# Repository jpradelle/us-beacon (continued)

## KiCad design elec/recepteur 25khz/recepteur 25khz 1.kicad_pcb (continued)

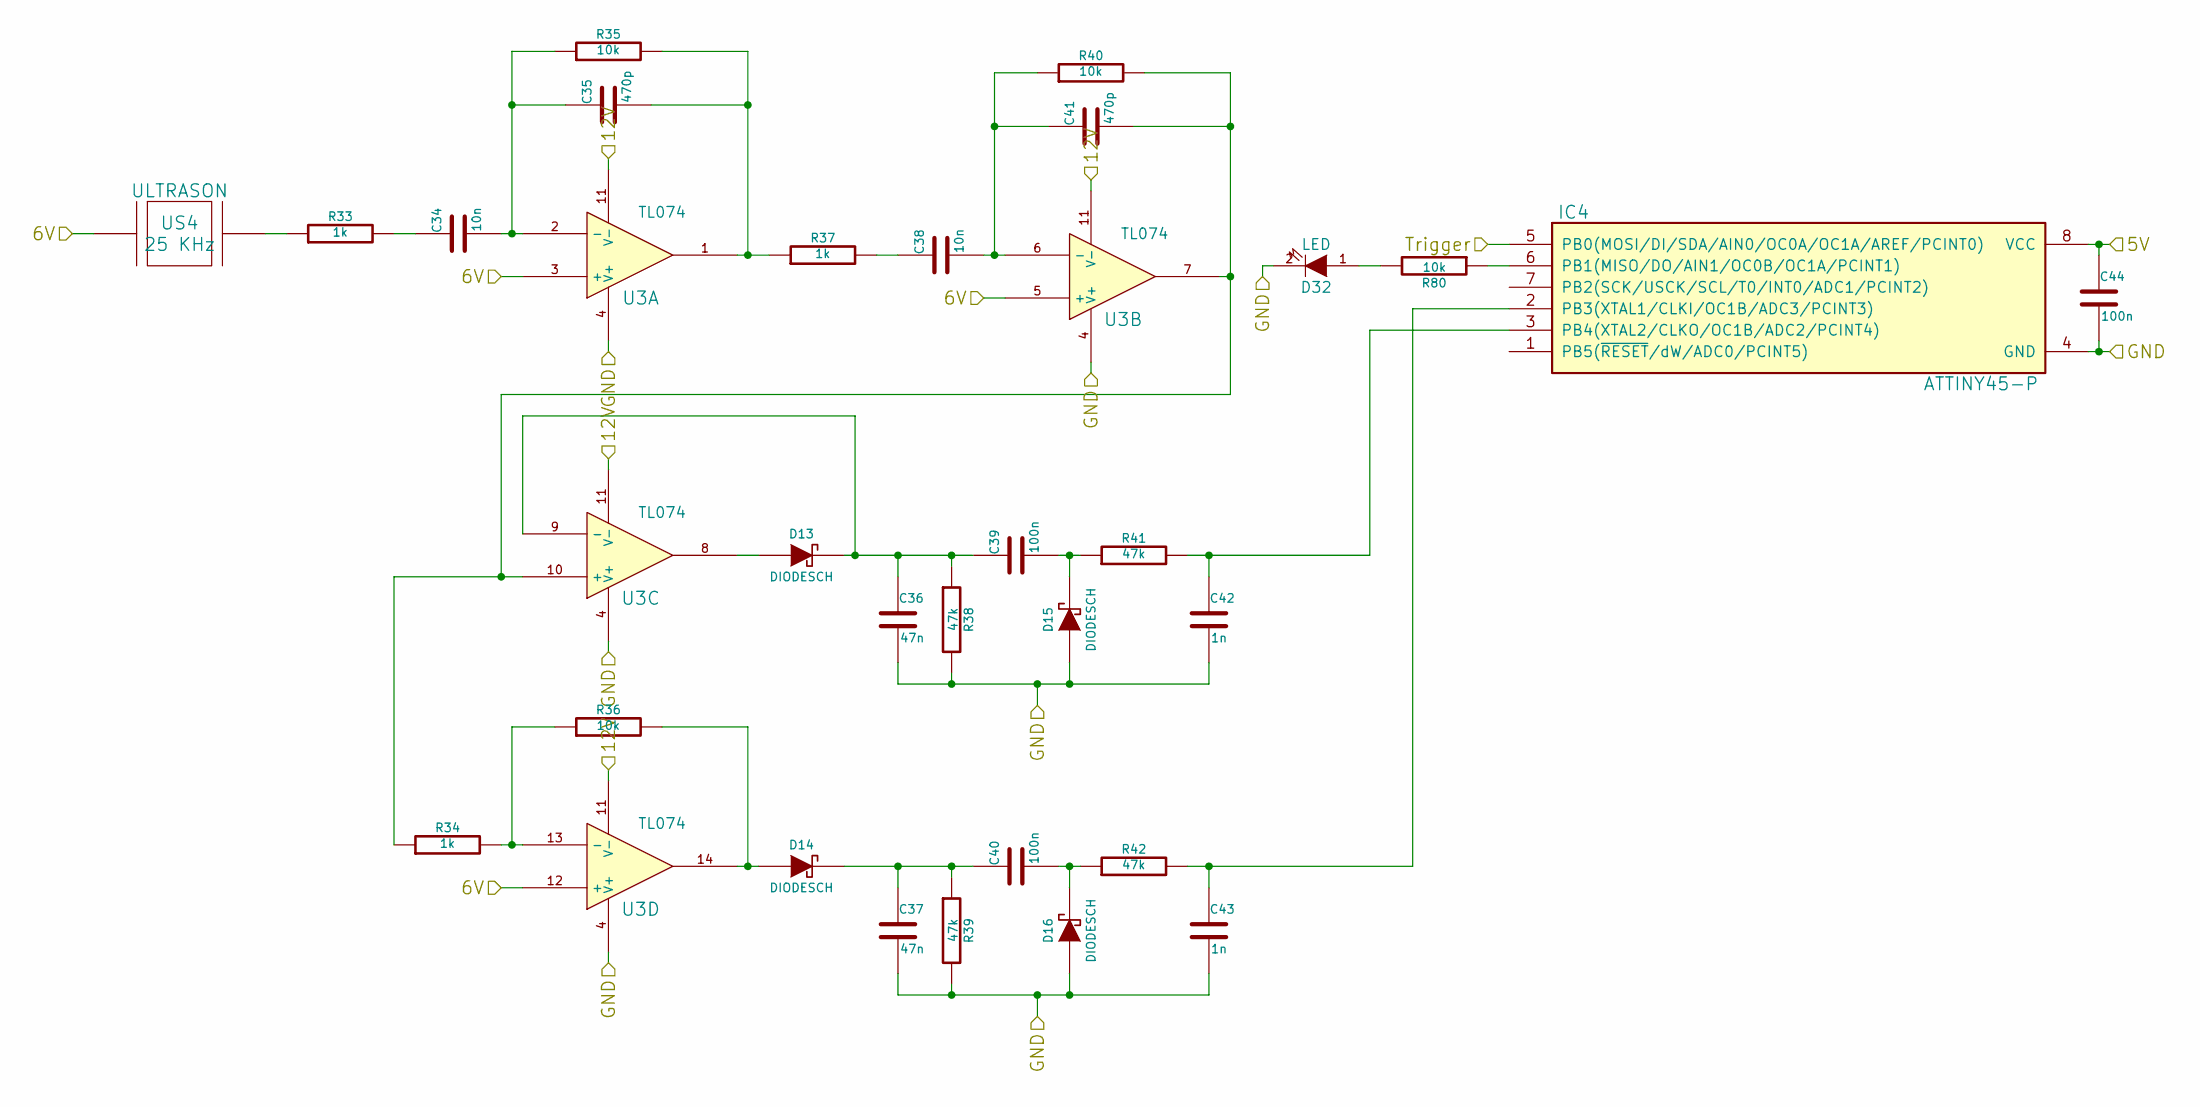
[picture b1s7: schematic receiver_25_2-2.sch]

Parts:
C34, C38: 10n
C35, C41: 470p
C36, C37: 47n
C39, C40, C44: 100n
C42, C43: 1n
D13, D14, D15, D16: DIODESCH
D32: LED
IC4: ATTINY45-P; DIP8
R33, R34, R37: 1k
R35, R36, R40, R80: 10k
R38, R39, R41, R42: 47k
U3: TL074
US4: ULTRASON

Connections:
/receiver_25_2-1/5V: C44.1, IC4.8 (VCC); also elsewhere on the board
/receiver_25_2-1/6V: U3.3 (+), U3.5 (+), U3.12 (+), US4.1; also elsewhere on the board
/receiver_25_2-1/12V: U3.11 (V-); also elsewhere on the board
/receiver_25_2-1/GND: C36.2, C37.2, C42.2, C43.2, C44.2, D15.1 (A), D16.1 (A), D32.2 (K), IC4.4 (GND), R38.2, R39.2, U3.4 (V+); also elsewhere on the board
/receiver_25_2-2/Trigger: IC4.5 (PB0(MOSI/DI/SDA/AIN0/OC0A/OC1A/AREF/PCI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); also elsewhere on the board
unnamed: C34.1, R33.2
unnamed: C34.2, C35.1, R35.1, U3.2 (-)
unnamed: C35.2, R35.2, R37.1, U3.1
unnamed: C36.1, C39.1, D13.2 (K), R38.1, U3.9 (-)
unnamed: C37.1, C40.1, D14.2 (K), R39.1
unnamed: C38.1, R37.2
unnamed: C38.2, C41.1, R40.1, U3.6 (-)
unnamed: C39.2, D15.2 (K), R41.1
unnamed: C40.2, D16.2 (K), R42.1
unnamed: C41.2, R34.1, R40.2, U3.7, U3.10 (+)
unnamed: C42.1, IC4.3 (PB4(XTAL2/CLKO/OC1B/ADC2/PCINT4)), R41.2
unnamed: C43.1, IC4.2 (PB3(XTAL1/CLKI/OC1B/ADC3/PCINT3)), R42.2
unnamed: D13.1 (A), U3.8
unnamed: D14.1 (A), R36.2, U3.14
unnamed: D32.1 (A), R80.2
unnamed: IC4.6 (PB1(MISO/DO/AIN1/OC0B/OC1A/PCINT1)), R80.1
unnamed: R33.1, US4.2
unnamed: R34.2, R36.1, U3.13 (-)

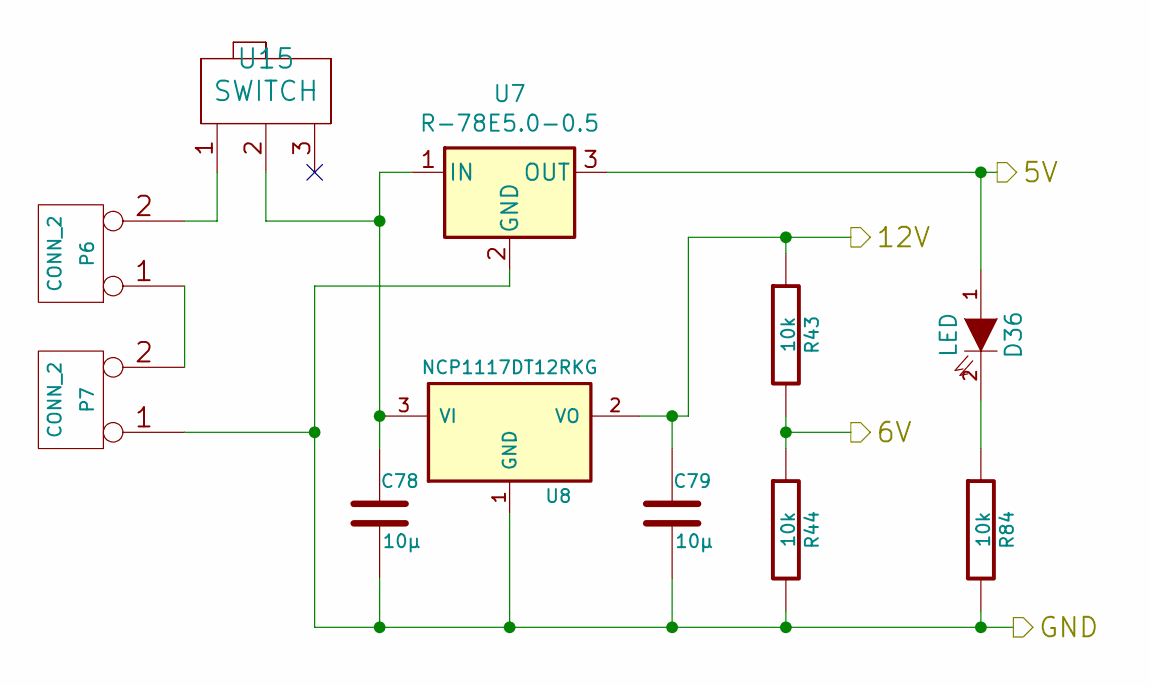
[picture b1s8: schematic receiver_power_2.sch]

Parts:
C78, C79: 10µ
D36: LED
P6, P7: CONN_2
R43, R44, R84: 10k
U7: R-78E5.0-0.5; Converter_DCDC_RECOM_R-78E-0.5_THT
U8: NCP1117DT12RKG
U15: SWITCH

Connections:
/receiver_power_2/5V: D36.1 (A), U7.3 (OUT); also elsewhere on the board
/receiver_power_2/6V: R43.2, R44.1; also elsewhere on the board
/receiver_power_2/12V: C79.1, R43.1, U8.2 (VO); also elsewhere on the board
/receiver_power_2/GND: C78.2, C79.2, P7.1, R44.2, R84.2, U7.2 (GND), U8.1 (GND); also elsewhere on the board
unnamed: C78.1, U7.1 (IN), U8.3 (VI), U15.2
unnamed: D36.2 (K), R84.1
unnamed: P6.1, P7.2 (PM)
unnamed: P6.2 (PM), U15.1

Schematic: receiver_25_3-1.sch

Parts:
C45, C49: 10n
C46, C52: 470p
C47, C48: 47n
C50, C51, C55: 100n
C53, C54: 1n
D17, D18, D19, D20: DIODESCH
D33: LED
IC5: ATTINY45-P; DIP8
R45, R46, R49: 1k
R47, R48, R52, R81: 10k
R50, R51, R53, R54: 47k
U9: TL074
US5: ULTRASON

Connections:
/receiver_25_3-1/5V: C55.1, IC5.8 (VCC); also elsewhere on the board
/receiver_25_3-1/6V: U9.3 (+), U9.5 (+), U9.12 (+), US5.1; also elsewhere on the board
/receiver_25_3-1/12V: U9.11 (V-); also elsewhere on the board
/receiver_25_3-1/GND: C47.2, C48.2, C53.2, C54.2, C55.2, D19.1 (A), D20.1 (A), D33.2 (K), IC5.4 (GND), R50.2, R51.2, U9.4 (V+); also elsewhere on the board
/receiver_25_3-1/Trigger: IC5.5 (PB0(MOSI/DI/SDA/AIN0/OC0A/OC1A/AREF/PCI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); also elsewhere on the board
unnamed: C45.1, R45.2
unnamed: C45.2, C46.1, R47.1, U9.2 (-)
unnamed: C46.2, R47.2, R49.1, U9.1
unnamed: C47.1, C50.1, D17.2 (K), R50.1, U9.9 (-)
unnamed: C48.1, C51.1, D18.2 (K), R51.1
unnamed: C49.1, R49.2
unnamed: C49.2, C52.1, R52.1, U9.6 (-)
unnamed: C50.2, D19.2 (K), R53.1
unnamed: C51.2, D20.2 (K), R54.1
unnamed: C52.2, R46.1, R52.2, U9.7, U9.10 (+)
unnamed: C53.1, IC5.3 (PB4(XTAL2/CLKO/OC1B/ADC2/PCINT4)), R53.2
unnamed: C54.1, IC5.2 (PB3(XTAL1/CLKI/OC1B/ADC3/PCINT3)), R54.2
unnamed: D17.1 (A), U9.8
unnamed: D18.1 (A), R48.2, U9.14
unnamed: D33.1 (A), R81.2
unnamed: IC5.6 (PB1(MISO/DO/AIN1/OC0B/OC1A/PCINT1)), R81.1
unnamed: R45.1, US5.2
unnamed: R46.2, R48.1, U9.13 (-)

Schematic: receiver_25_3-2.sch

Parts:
C56, C60: 10n
C57, C63: 470p
C58, C59: 47n
C61, C62, C66: 100n
C64, C65: 1n
D21, D22, D23, D24: DIODESCH
D34: LED
IC6: ATTINY45-P; DIP8
R55, R56, R59: 1k
R57, R58, R62, R82: 10k
R60, R61, R63, R64: 47k
U10: TL074
US6: ULTRASON

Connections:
/receiver_25_3-1/5V: C66.1, IC6.8 (VCC); also elsewhere on the board
/receiver_25_3-1/6V: U10.3 (+), U10.5 (+), U10.12 (+), US6.1; also elsewhere on the board
/receiver_25_3-1/12V: U10.11 (V-); also elsewhere on the board
/receiver_25_3-1/GND: C58.2, C59.2, C64.2, C65.2, C66.2, D23.1 (A), D24.1 (A), D34.2 (K), IC6.4 (GND), R60.2, R61.2, U10.4 (V+); also elsewhere on the board
/receiver_25_3-2/Trigger: IC6.5 (PB0(MOSI/DI/SDA/AIN0/OC0A/OC1A/AREF/PCI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); also elsewhere on the board
unnamed: C56.1, R55.2
unnamed: C56.2, C57.1, R57.1, U10.2 (-)
unnamed: C57.2, R57.2, R59.1, U10.1
unnamed: C58.1, C61.1, D21.2 (K), R60.1, U10.9 (-)
unnamed: C59.1, C62.1, D22.2 (K), R61.1
unnamed: C60.1, R59.2
unnamed: C60.2, C63.1, R62.1, U10.6 (-)
unnamed: C61.2, D23.2 (K), R63.1
unnamed: C62.2, D24.2 (K), R64.1
unnamed: C63.2, R56.1, R62.2, U10.7, U10.10 (+)
unnamed: C64.1, IC6.3 (PB4(XTAL2/CLKO/OC1B/ADC2/PCINT4)), R63.2
unnamed: C65.1, IC6.2 (PB3(XTAL1/CLKI/OC1B/ADC3/PCINT3)), R64.2
unnamed: D21.1 (A), U10.8
unnamed: D22.1 (A), R58.2, U10.14
unnamed: D34.1 (A), R82.2
unnamed: IC6.6 (PB1(MISO/DO/AIN1/OC0B/OC1A/PCINT1)), R82.1
unnamed: R55.1, US6.2
unnamed: R56.2, R58.1, U10.13 (-)

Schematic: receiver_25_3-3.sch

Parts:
C67, C71: 10n
C68, C74: 470p
C69, C70: 47n
C72, C73, C77: 100n
C75, C76: 1n
D25, D26, D27, D28: DIODESCH
D35: LED
IC7: ATTINY45-P; DIP8
R65, R66, R69: 1k
R67, R68, R72, R83: 10k
R70, R71, R73, R74: 47k
U11: TL074
US7: ULTRASON

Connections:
/receiver_25_3-1/5V: C77.1, IC7.8 (VCC); also elsewhere on the board
/receiver_25_3-1/6V: U11.3 (+), U11.5 (+), U11.12 (+), US7.1; also elsewhere on the board
/receiver_25_3-1/12V: U11.11 (V-); also elsewhere on the board
/receiver_25_3-1/GND: C69.2, C70.2, C75.2, C76.2, C77.2, D27.1 (A), D28.1 (A), D35.2 (K), IC7.4 (GND), R70.2, R71.2, U11.4 (V+); also elsewhere on the board
/receiver_25_3-3/Trigger: IC7.5 (PB0(MOSI/DI/SDA/AIN0/OC0A/OC1A/AREF/PCI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); also elsewhere on the board
unnamed: C67.1, R65.2
unnamed: C67.2, C68.1, R67.1, U11.2 (-)
unnamed: C68.2, R67.2, R69.1, U11.1
unnamed: C69.1, C72.1, D25.2 (K), R70.1, U11.9 (-)
unnamed: C70.1, C73.1, D26.2 (K), R71.1
unnamed: C71.1, R69.2
unnamed: C71.2, C74.1, R72.1, U11.6 (-)
unnamed: C72.2, D27.2 (K), R73.1
unnamed: C73.2, D28.2 (K), R74.1
unnamed: C74.2, R66.1, R72.2, U11.7, U11.10 (+)
unnamed: C75.1, IC7.3 (PB4(XTAL2/CLKO/OC1B/ADC2/PCINT4)), R73.2
unnamed: C76.1, IC7.2 (PB3(XTAL1/CLKI/OC1B/ADC3/PCINT3)), R74.2
unnamed: D25.1 (A), U11.8
unnamed: D26.1 (A), R68.2, U11.14
unnamed: D35.1 (A), R83.2
unnamed: IC7.6 (PB1(MISO/DO/AIN1/OC0B/OC1A/PCINT1)), R83.1
unnamed: R65.1, US7.2
unnamed: R66.2, R68.1, U11.13 (-)

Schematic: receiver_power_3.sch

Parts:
C82, C83: 10µ
D37: LED
P12, P13: CONN_2
R75, R76, R85: 10k
U12: R-78E5.0-0.5; Converter_DCDC_RECOM_R-78E-0.5_THT
U13: NCP1117DT12RKG
U16: SWITCH

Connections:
/receiver_power_3/5V: D37.1 (A), U12.3 (OUT); also elsewhere on the board
/receiver_power_3/6V: R75.2, R76.1; also elsewhere on the board
/receiver_power_3/12V: C83.1, R75.1, U13.2 (VO); also elsewhere on the board
/receiver_power_3/GND: C82.2, C83.2, P13.1, R76.2, R85.2, U12.2 (GND), U13.1 (GND); also elsewhere on the board
unnamed: C82.1, U12.1 (IN), U13.3 (VI), U16.2
unnamed: D37.2 (K), R85.1
unnamed: P12.1, P13.2 (PM)
unnamed: P12.2 (PM), U16.1

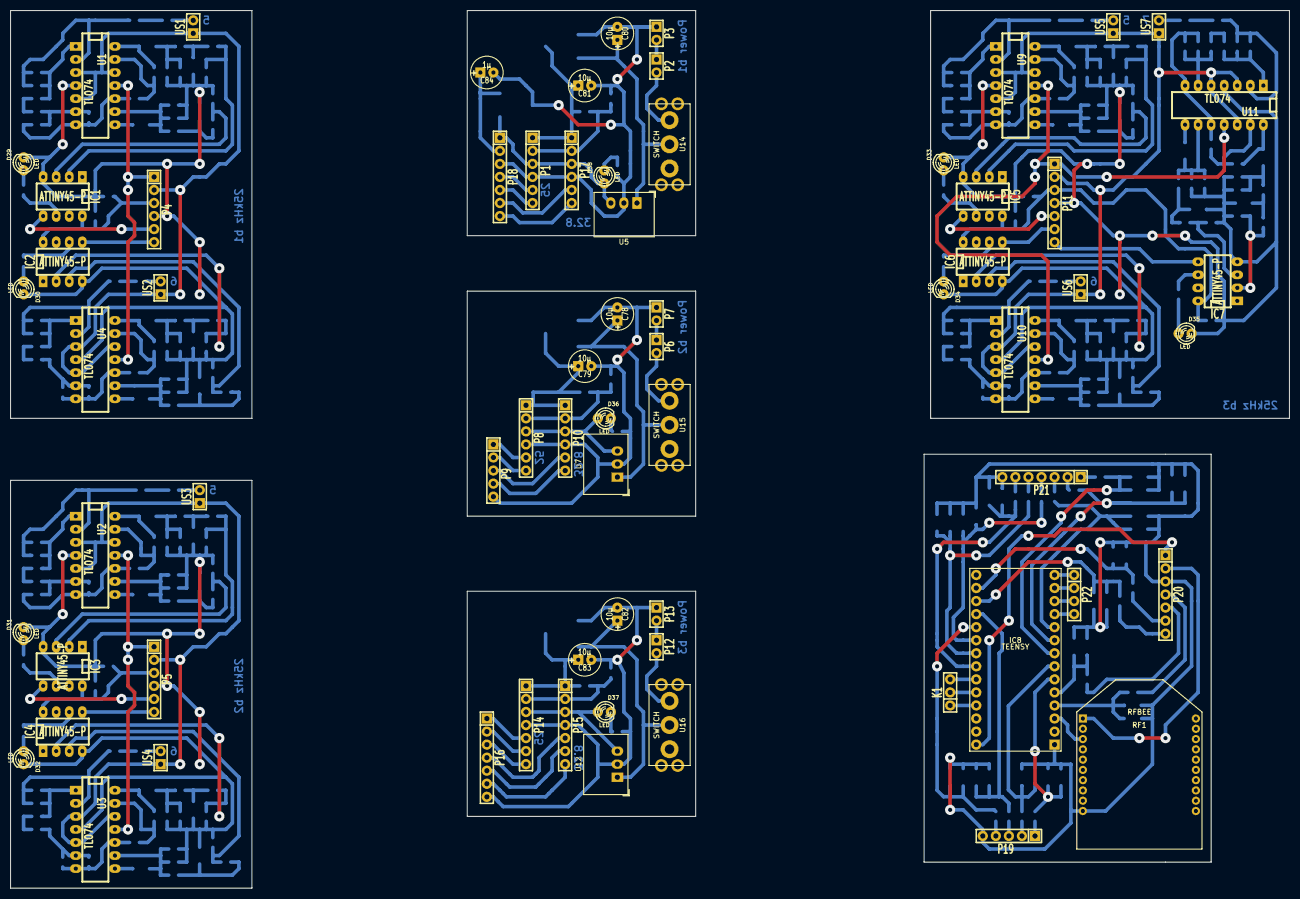
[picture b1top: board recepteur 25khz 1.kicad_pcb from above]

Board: 2 copper layers, 248.9 x 170.8 mm, 306 parts (0 on the bottom side), 223 nets.

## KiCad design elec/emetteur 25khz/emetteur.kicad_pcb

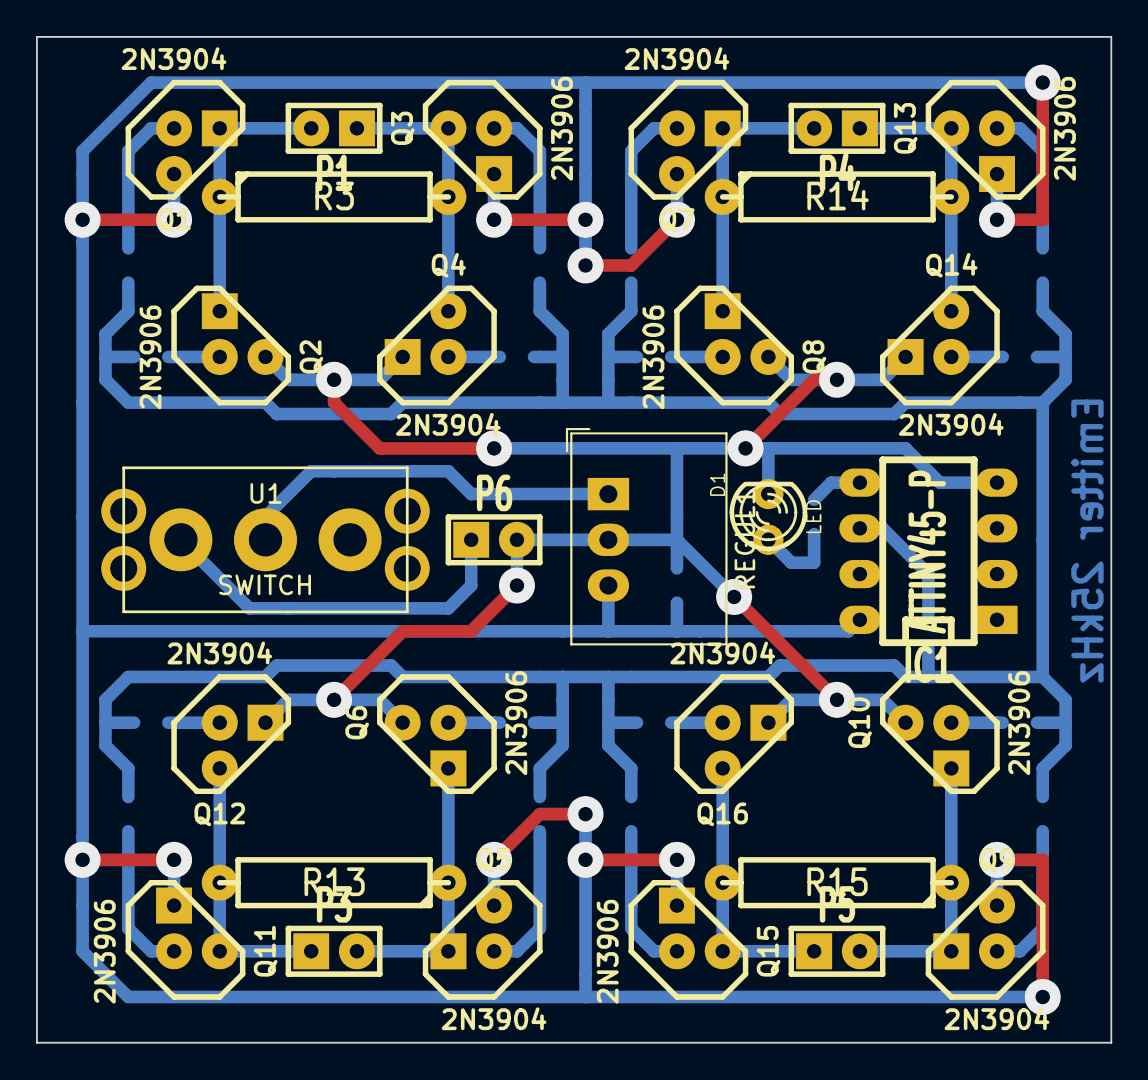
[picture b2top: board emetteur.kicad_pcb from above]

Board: 2 copper layers, 59.7 x 55.9 mm, 48 parts (0 on the bottom side), 32 nets.

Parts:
C1: 100n; SM0805
D1: LED; LED-3MM
IC1: ATTINY45-P; DIP-8__300_ELL
P1, P3, P4, P5, P6: CONN_2; SIL-2
Q1, Q4, Q5, Q7, Q9, Q12, Q14, Q16: 2N3904; TO92
Q2, Q3, Q6, Q8, Q10, Q11, Q13, Q15: 2N3906; TO92
R1, R2, R4, R5, R7, R8, R9, R10, R11, R12, R16, R17, R18, R19, R20, R21: 22k; SM0805
R3, R13, R14, R15: 1k; R5
R6: 1k; SM0805
R22: 10k; SM0805
REGUL1: R-78E5.0-0.5; Converter_DCDC_RECOM_R-78E-0.5_THT
U1: SWITCH; switch

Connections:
+9V: P6.1, U1.1
GND: C1.2, D1.2, IC1.4, P6.2, Q2.3, Q4.1, Q6.3, Q8.3, Q10.3, Q12.1, Q14.1, Q16.1, REGUL1.2
unnamed: D1.1, R22.1
unnamed: IC1.5, R22.2
unnamed: IC1.6, R6.2
unnamed: P1.1, Q3.3, Q4.3, R3.2
unnamed: P1.2, Q1.1, Q2.1, R3.1
unnamed: P3.1, Q11.3, Q12.3, R13.2
unnamed: P3.2, Q5.1, Q6.1, R13.1
unnamed: P4.1, Q13.3, Q14.3, R14.2
unnamed: P4.2, Q7.1, Q8.1, R14.1
unnamed: P5.1, Q15.3, Q16.3, R15.2
unnamed: P5.2, Q9.1, Q10.1, R15.1
unnamed: Q1.2, R1.2
unnamed: Q2.2, R2.2
unnamed: Q3.2, R4.1
unnamed: Q4.2, R5.1
unnamed: Q5.2, R7.2
unnamed: Q6.2, R8.2
unnamed: Q7.2, R9.2
unnamed: Q8.2, R10.2
unnamed: Q9.2, R11.2
unnamed: Q10.2, R12.2
unnamed: Q11.2, R16.1
unnamed: Q12.2, R17.1
unnamed: Q13.2, R18.1
unnamed: Q14.2, R19.1
unnamed: Q15.2, R20.1
unnamed: Q16.2, R21.1
unnamed: R1.1, R2.1, R4.2, R5.2, R6.1, R7.1, R8.1, R9.1, R10.1, R11.1, R12.1, R16.2, R17.2, R18.2, R19.2, R20.2, R21.2
unnamed: REGUL1.1, U1.2
VCC: C1.1, IC1.8, Q1.3, Q3.1, Q5.3, Q7.3, Q9.3, Q11.1, Q13.1, Q15.1, REGUL1.3

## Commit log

2023-06-05 Project init from archive, Kicad update from 2013 version to verion 5
2023-06-06 Add some documentation
2023-06-06 Simu: update ImageSimu runner
2023-06-06 Simu: add some documentation
2023-06-06 Simu: add max error graph
2023-06-06 Simu: write documentation
2023-06-06 Simu: fix TOA Circle wrong simulation image
2023-06-09 Elec: add readme
